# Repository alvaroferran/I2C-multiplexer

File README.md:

# I2C Multiplexer
#### PCA9548 i2c multiplexer board and library

&nbsp;

This repository contains the multiplexer board and  an arduino library. 

This module is useful when multiple i2c devices must be connected to a microcontroller but share fixed addresses, for example using several identical sensors with the same hardware-defined address. To solve this connect each offending sensor to different i2c buses and simply select the appropiate channel before communicating with the device as usual.

#### BOARD

·The board has one input i2c channel and eight output ones. The input works at 5V level while the rest work at 3.3V.
&nbsp;
·It has eight possible, hardware-defined I2C addresses, which are selectable through three solder pads, as in the following table:

| A2 | A1 | A0 | I2C Address |
| :---: | :---: | :---: | :---------: |
| 0  | 0  | 0  |    0X70     |
| 0  | 0  | 1  |    0X71     |
| 0  | 1  | 0  |    0X72     |
| 0  | 1  | 1  |    0X73     |
| 1  | 0  | 0  |    0X74     |
| 1  | 0  | 1  |    0X75     |
| 1  | 1  | 0  |    0X76     |
| 1  | 1  | 1  |    0X77     |

&nbsp;
·The pads on next to each connector enables that bus' 4.7k pullup resistors. These pads should be soldered if there were no other pullup resistors on the bus.
&nbsp;

#### LIBRARY

· To install the library simply copy the folder "I2CMux" into your folder "sketchbook/libraries/".

&nbsp;

· The module's address is passed to the constructor, while the channel is selected by the method "switchToBus(busNumber)", with busNumber between 0 and 7.

&nbsp;

· In the "examples" subfolder an example sketch is available which demonstrates how to switch between different i2c channels, reading data from two [BNO055](https://github.com/bqlabs/BNO055) sensors with the same address in different buses.

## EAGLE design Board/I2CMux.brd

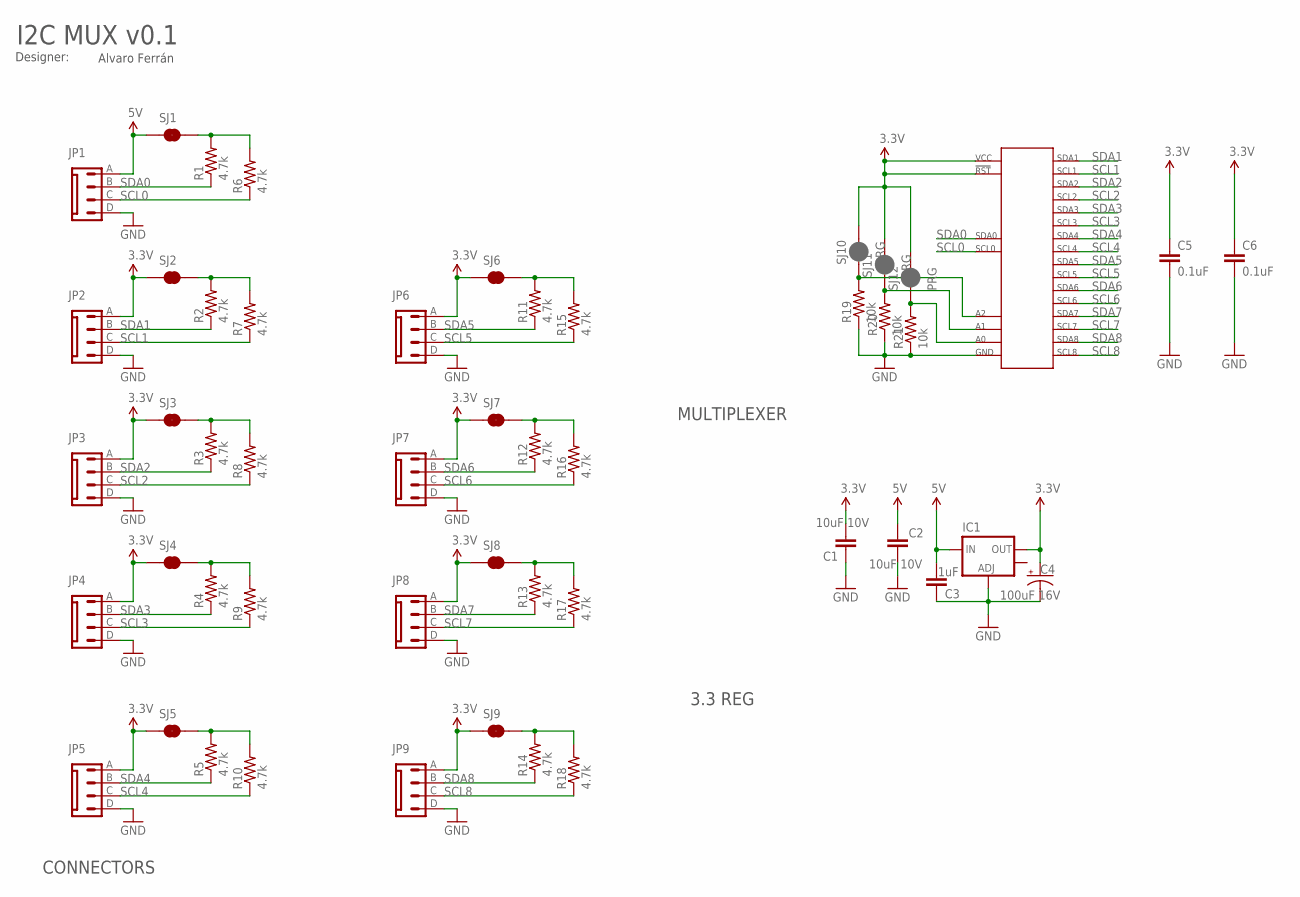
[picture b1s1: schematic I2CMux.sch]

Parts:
C1, C2: 10uF 10V; 0402-CAP
C3: 1uF; 0402-CAP
C4: 100uF 16V; PANASONIC_C
C5, C6: 0.1uF; 0402-CAP
IC1: V_REG_LM1117SOT223; SOT223
IC2: PCA9548A; PCA9548ABS
JP1, JP2, JP3, JP4, JP5, JP6, JP7, JP8, JP9: MX-6410-04A
R1, R2, R3, R4, R5, R6, R7, R8, R9, R10, R11, R12, R13, R14, R15, R16, R17, R18: 4.7k; 0402-RES
R19, R20, R21: 10k; 0402-RES
SJ1, SJ2, SJ3, SJ4, SJ5, SJ6, SJ7, SJ8, SJ9: JUMPER-PAD-2-NC_BY_TRACE; PAD-JUMPER-2-NC_BY_TRACE_YES_SILK
SJ10, SJ11, SJ12: PRG; PAD-JUMPER-2-NC_BY_PASTE_YES_SILK

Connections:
3.3V: C1.2, C4.+, C5.1, C6.1, IC1.2 (OUT), IC2.21 (VCC), IC2.24 (!RESET), JP2.A, JP3.A, JP4.A, JP5.A, JP6.A, JP7.A, JP8.A, JP9.A, SJ2.1, SJ3.1, SJ4.1, SJ5.1, SJ6.1, SJ7.1, SJ8.1, SJ9.1, SJ10.2, SJ11.2, SJ12.2
5V: C2.2, C3.2, IC1.3 (IN), JP1.A, SJ1.1
A0: IC2.22 (A0), R21.2, SJ12.1
A1: IC2.23 (A1), R20.2, SJ11.1
A2: IC2.18 (A2), R19.2, SJ10.1
GND: C1.1, C2.1, C3.1, C4.-, C5.2, C6.2, IC1.1 (ADJ), IC2.9 (GND), IC2.THERMAL (GND), JP1.D, JP2.D, JP3.D, JP4.D, JP5.D, JP6.D, JP7.D, JP8.D, JP9.D, R19.1, R20.1, R21.1
unnamed: R1.2, R6.2, SJ1.2
unnamed: R2.2, R7.2, SJ2.2
unnamed: R3.2, R8.2, SJ3.2
unnamed: R4.2, R9.2, SJ4.2
unnamed: R5.2, R10.2, SJ5.2
unnamed: R14.2, R18.2, SJ9.2
unnamed: R13.2, R17.2, SJ8.2
unnamed: R12.2, R16.2, SJ7.2
unnamed: R11.2, R15.2, SJ6.2
SCL0: IC2.19 (SCL0), JP1.C, R6.1
SCL1: IC2.2 (SCL1), JP2.C, R7.1
SCL2: IC2.4 (SCL2), JP3.C, R8.1
SCL3: IC2.6 (SCL3), JP4.C, R9.1
SCL4: IC2.8 (SCL4), JP5.C, R10.1
SCL5: IC2.11 (SCL5), JP6.C, R15.1
SCL6: IC2.13 (SCL6), JP7.C, R16.1
SCL7: IC2.15 (SCL7), JP8.C, R17.1
SCL8: IC2.17 (SCL8), JP9.C, R18.1
SDA0: IC2.20 (SDA0), JP1.B, R1.1
SDA1: IC2.1 (SDA1), JP2.B, R2.1
SDA2: IC2.3 (SDA2), JP3.B, R3.1
SDA3: IC2.5 (SDA3), JP4.B, R4.1
SDA4: IC2.7 (SDA4), JP5.B, R5.1
SDA5: IC2.10 (SDA5), JP6.B, R11.1
SDA6: IC2.12 (SDA6), JP7.B, R12.1
SDA7: IC2.14 (SDA7), JP8.B, R13.1
SDA8: IC2.16 (SDA8), JP9.B, R14.1

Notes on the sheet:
I2C MUX v0.1
Designer:
Alvaro Ferrán
MULTIPLEXER
3.3 REG
CONNECTORS

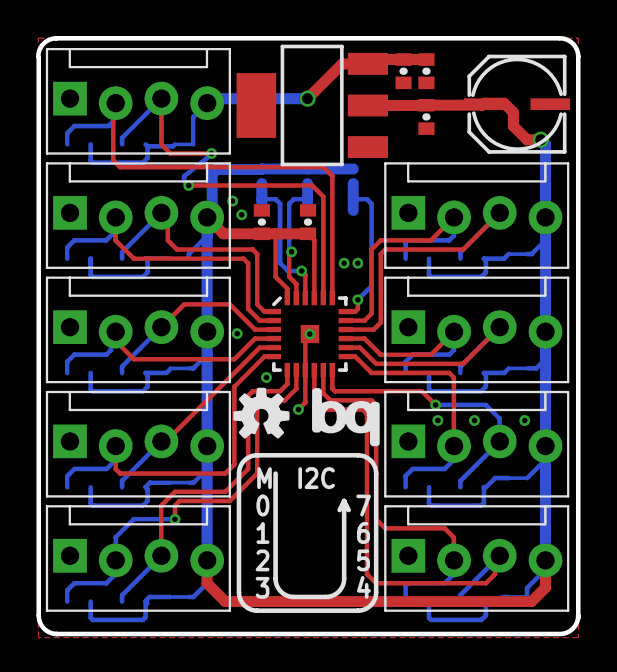
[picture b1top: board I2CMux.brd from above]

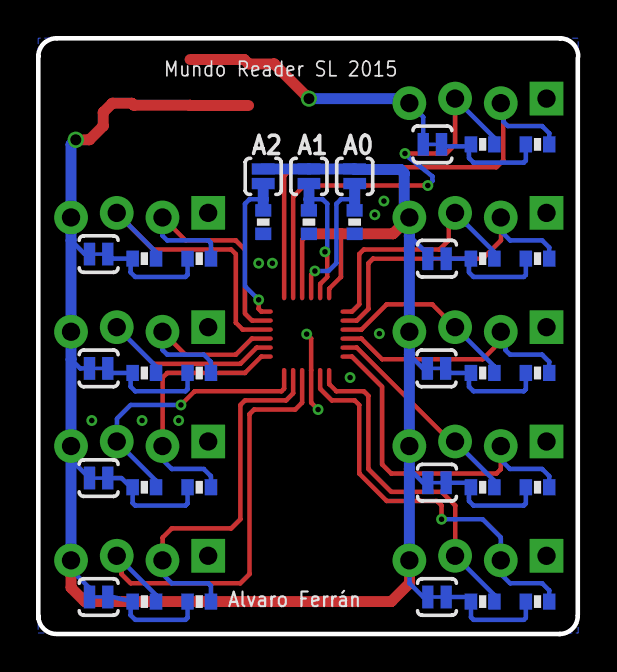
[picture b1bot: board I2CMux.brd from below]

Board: 2 copper layers, 30.0 x 33.1 mm, 52 parts (33 on the bottom side), 33 nets.

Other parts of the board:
LOGO3: OSHW-LOGOS; OSHW-LOGO-S
U$2: BQ_LOGO_MEDIUM

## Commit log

2015-10-27 Board and library added
2015-10-27 Readme updated
2016-03-14 json added

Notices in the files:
parts and their libraries:
SparkFun-Capacitors: Licensing: Creative Commons ShareAlike 4.0 International - https://creativecommons.org/licenses/by-sa/4.0
